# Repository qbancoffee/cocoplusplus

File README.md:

# CoCo++
I spent some time transcribing the CoCo 3 schematic into KiCAD to contribute to the bit preserve project.
Using that schematic, I created a drop in replacement board which I subsequently ordered, assembled, and tested.
At this point I consider that project done and time to move on. If you are interested in the bit preserve
project here is the link.<br>
[Bit Preserve, recreating classic computer schematics](https://github.com/baldengineer/bit-preserve)

So now it's time to have fun....<br>
I want to base this board on the CoCo 3 for several reasons.

- It's the latest real CoCo.
- I never used one in my youth.
- When people upgrade to to the GIME-X, they may want to use their otherwise unused GIME
- If used with a GIME-X then there would be a new CoCo added to the world. 

To start this I stripped the CoCo 3 portion out of the bit-preserve project and
created this repository so that I could make changes to the board that I would like to see. I'm making
this available so that anyone can contribute ideas and expertise.

### Goals
I still don't know what all of the goals are but I'll list some ideas that I've had or that others have mentioned or recommended.
- Having fun
- Mod for potential DMA
- USB keyboard
- Reduce overall size 
- A different form factor
- [Fit it in a polycase ZN-45](https://www.polycase.com/zn-45)
- HDMI or VGA out
- Composite out
- Surface mount components
- 12V power supply with standard barrel connector
- Replace DAC/ADC chip with equivalent circuitry
- Replace SALT chip with equivalent circuitry

### Videos
- [Testing new CoCo 3 board](https://youtu.be/XzGmMZHgejc)
- [Running NitrOS 9 Ease Of Use](https://youtu.be/wSlYcxvCpys)

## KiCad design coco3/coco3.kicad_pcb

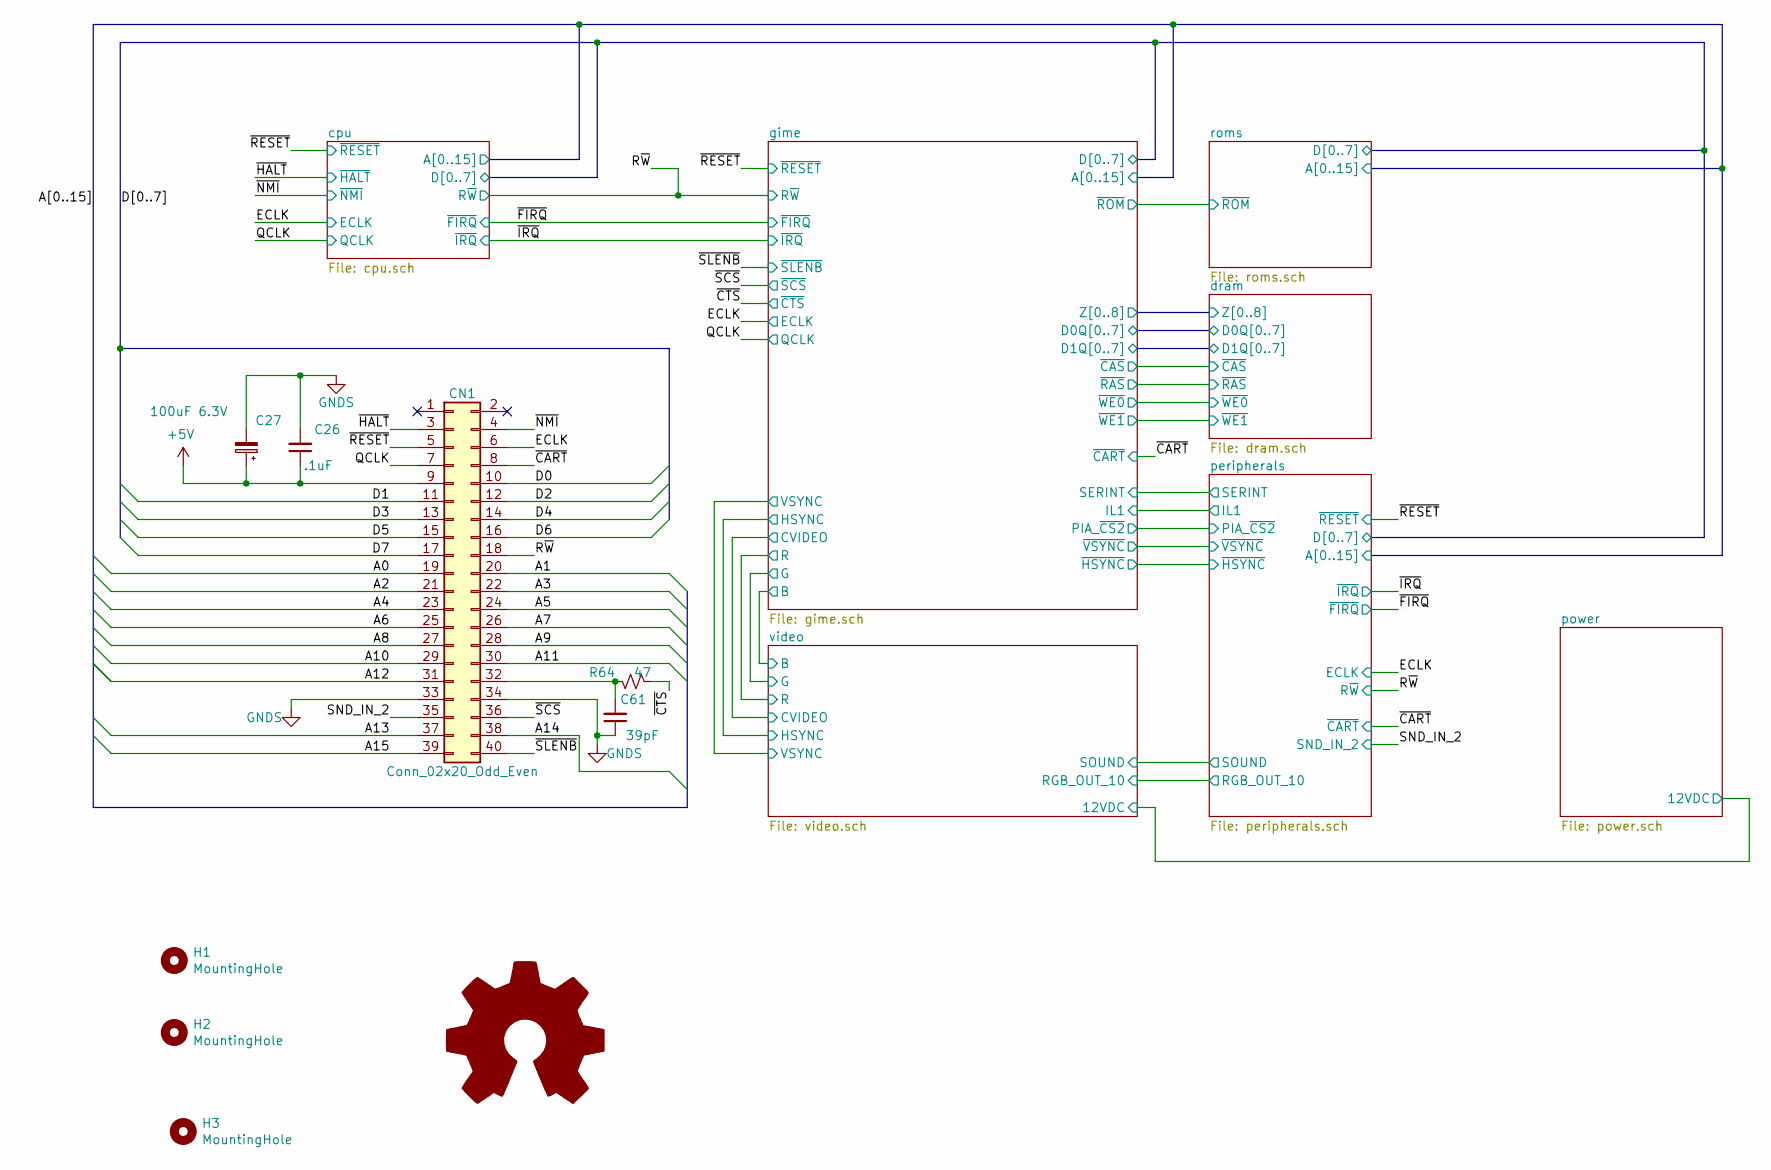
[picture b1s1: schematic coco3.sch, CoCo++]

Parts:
C26: .1uF; C_0805_2012Metric_Pad1.18x1.45mm_HandSolder; Manufacturer part# CL21A106KAYNNNE
C27: 100uF 6.3V; CP_EIA-3528-21_Kemet-B; Manufacturer part# TAJB107K006RNJ
C61: 39pF; C_0805_2012Metric_Pad1.18x1.45mm_HandSolder; Manufacturer part# 0805N390J500CT
CN1: Conn_02x20_Odd_Even; EBC20DRAS; Manufacturer part# EBC20DRAS
H1, H2: MountingHole; MountingHole_3.5mm
H3: MountingHole; coco3_outline_and_layout
R64: 47; R_1206_3216Metric_Pad1.30x1.75mm_HandSolder; Manufacturer part# 1206W4J0470T5E

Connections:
+5V: C26.1, C27.1, CN1.9; also elsewhere on the board
/A0: CN1.19; also elsewhere on the board
/A1: CN1.20; also elsewhere on the board
/A2: CN1.21; also elsewhere on the board
/A3: CN1.22; also elsewhere on the board
/A4: CN1.23; also elsewhere on the board
/A5: CN1.24; also elsewhere on the board
/A6: CN1.25; also elsewhere on the board
/A7: CN1.26; also elsewhere on the board
/A8: CN1.27; also elsewhere on the board
/A9: CN1.28; also elsewhere on the board
/A10: CN1.29; also elsewhere on the board
/A11: CN1.30; also elsewhere on the board
/A12: CN1.31; also elsewhere on the board
/A13: CN1.37; also elsewhere on the board
/A14: CN1.38; also elsewhere on the board
/A15: CN1.39; also elsewhere on the board
/D0: CN1.10; also elsewhere on the board
/D1: CN1.11; also elsewhere on the board
/D2: CN1.12; also elsewhere on the board
/D3: CN1.13; also elsewhere on the board
/D4: CN1.14; also elsewhere on the board
/D5: CN1.15; also elsewhere on the board
/D6: CN1.16; also elsewhere on the board
/D7: CN1.17; also elsewhere on the board
/ECLK: CN1.6; also elsewhere on the board
/QCLK: CN1.7; also elsewhere on the board
/R~W: CN1.18; also elsewhere on the board
/SND_IN_2: CN1.35; also elsewhere on the board
/~CART: CN1.8; also elsewhere on the board
/~CTS: R64.1; also elsewhere on the board
/~HALT: CN1.3; also elsewhere on the board
/~NMI: CN1.4; also elsewhere on the board
/~RESET: CN1.5; also elsewhere on the board
/~SCS: CN1.36; also elsewhere on the board
/~SLENB: CN1.40; also elsewhere on the board
unnamed: C61.2, CN1.32, R64.2

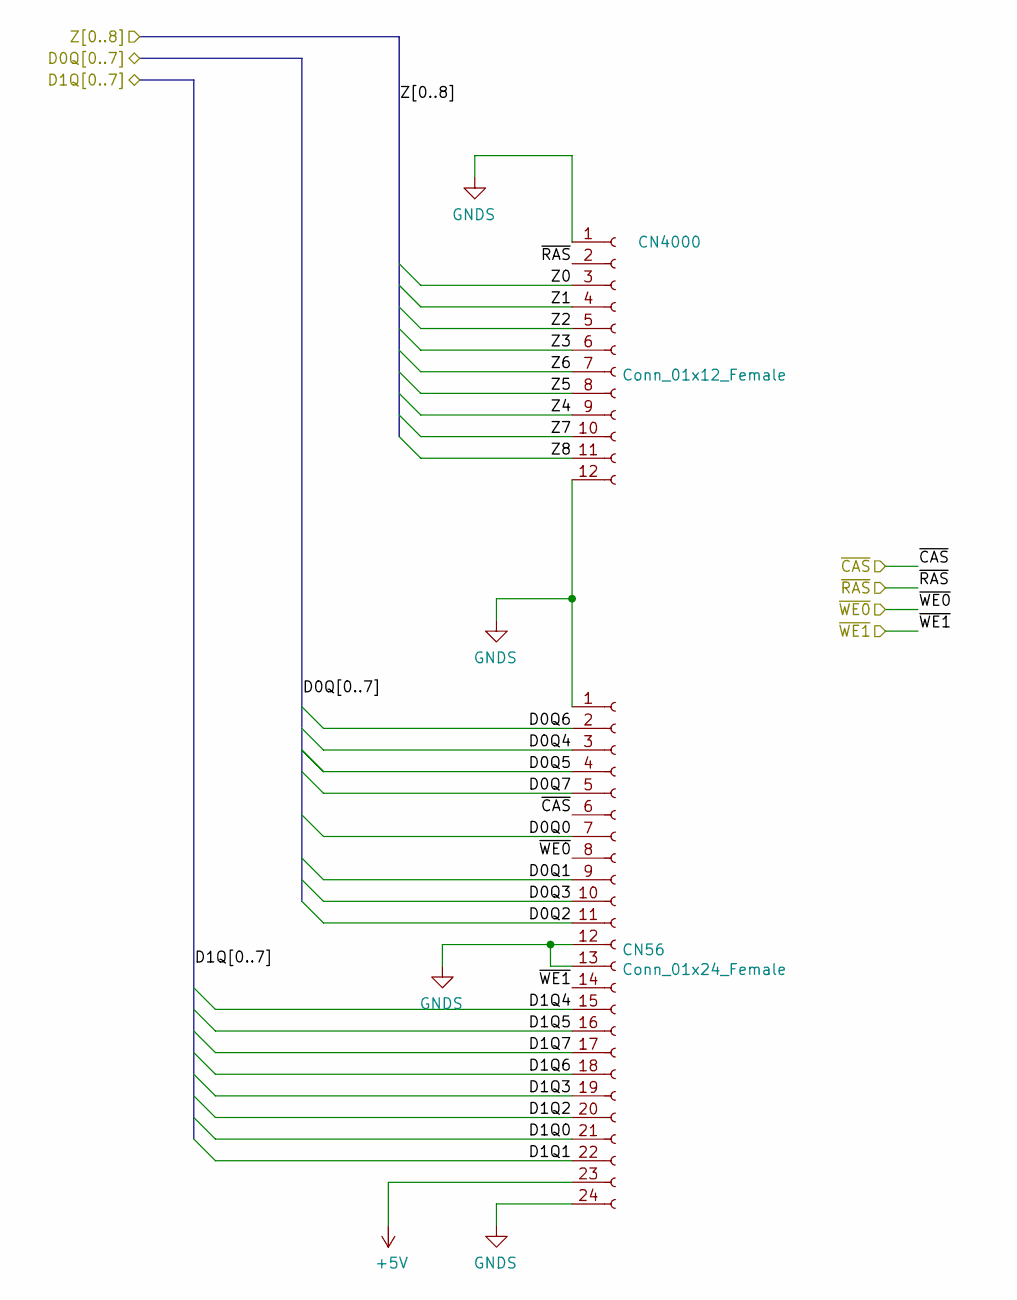
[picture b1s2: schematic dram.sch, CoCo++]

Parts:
CN56: Conn_01x24_Female; PinSocket_1x24_P2.54mm_Vertical; Manufacturer part# PPTC241LFBN-RC
CN4000: Conn_01x12_Female; PinSocket_1x12_P2.54mm_Vertical; Manufacturer part# PPTC121LFBN-RC

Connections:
+5V: CN56.23; also elsewhere on the board
/dram/D0Q0: CN56.7; also elsewhere on the board
/dram/D0Q1: CN56.9; also elsewhere on the board
/dram/D0Q2: CN56.11; also elsewhere on the board
/dram/D0Q3: CN56.10; also elsewhere on the board
/dram/D0Q4: CN56.3; also elsewhere on the board
/dram/D0Q5: CN56.4; also elsewhere on the board
/dram/D0Q6: CN56.2; also elsewhere on the board
/dram/D0Q7: CN56.5; also elsewhere on the board
/dram/D1Q0: CN56.21; also elsewhere on the board
/dram/D1Q1: CN56.22; also elsewhere on the board
/dram/D1Q2: CN56.20; also elsewhere on the board
/dram/D1Q3: CN56.19; also elsewhere on the board
/dram/D1Q4: CN56.15; also elsewhere on the board
/dram/D1Q5: CN56.16; also elsewhere on the board
/dram/D1Q6: CN56.18; also elsewhere on the board
/dram/D1Q7: CN56.17; also elsewhere on the board
/dram/Z0: CN4000.3; also elsewhere on the board
/dram/Z1: CN4000.4; also elsewhere on the board
/dram/Z2: CN4000.5; also elsewhere on the board
/dram/Z3: CN4000.6; also elsewhere on the board
/dram/Z4: CN4000.9; also elsewhere on the board
/dram/Z5: CN4000.8; also elsewhere on the board
/dram/Z6: CN4000.7; also elsewhere on the board
/dram/Z7: CN4000.10; also elsewhere on the board
/dram/Z8: CN4000.11; also elsewhere on the board
/dram/~CAS: CN56.6; also elsewhere on the board
/dram/~RAS: CN4000.2; also elsewhere on the board
/dram/~WE0: CN56.8; also elsewhere on the board
/dram/~WE1: CN56.14; also elsewhere on the board

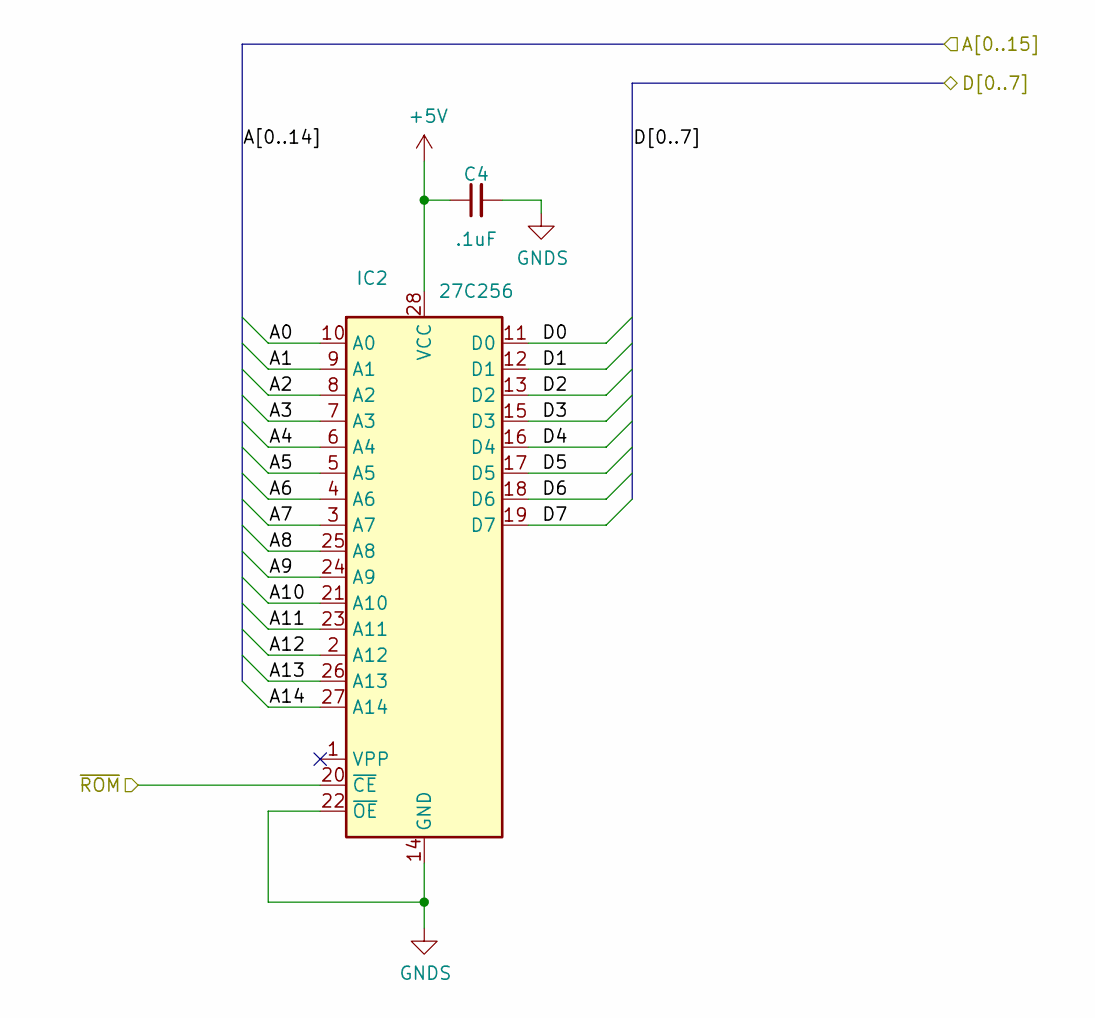
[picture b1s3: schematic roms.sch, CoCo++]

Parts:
C4: .1uF; C_0805_2012Metric_Pad1.18x1.45mm_HandSolder; Manufacturer part# CL21A106KAYNNNE
IC2: 27C256; DIP-28_W15.24mm_Socket; Manufacturer part# AT27C256R-45PU

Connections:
+5V: C4.1, IC2.28 (VCC); also elsewhere on the board
/A0: IC2.10 (A0); also elsewhere on the board
/A1: IC2.9 (A1); also elsewhere on the board
/A2: IC2.8 (A2); also elsewhere on the board
/A3: IC2.7 (A3); also elsewhere on the board
/A4: IC2.6 (A4); also elsewhere on the board
/A5: IC2.5 (A5); also elsewhere on the board
/A6: IC2.4 (A6); also elsewhere on the board
/A7: IC2.3 (A7); also elsewhere on the board
/A8: IC2.25 (A8); also elsewhere on the board
/A9: IC2.24 (A9); also elsewhere on the board
/A10: IC2.21 (A10); also elsewhere on the board
/A11: IC2.23 (A11); also elsewhere on the board
/A12: IC2.2 (A12); also elsewhere on the board
/A13: IC2.26 (A13); also elsewhere on the board
/A14: IC2.27 (A14); also elsewhere on the board
/D0: IC2.11 (D0); also elsewhere on the board
/D1: IC2.12 (D1); also elsewhere on the board
/D2: IC2.13 (D2); also elsewhere on the board
/D3: IC2.15 (D3); also elsewhere on the board
/D4: IC2.16 (D4); also elsewhere on the board
/D5: IC2.17 (D5); also elsewhere on the board
/D6: IC2.18 (D6); also elsewhere on the board
/D7: IC2.19 (D7); also elsewhere on the board
/gime/~ROM: IC2.20 (~CE); also elsewhere on the board

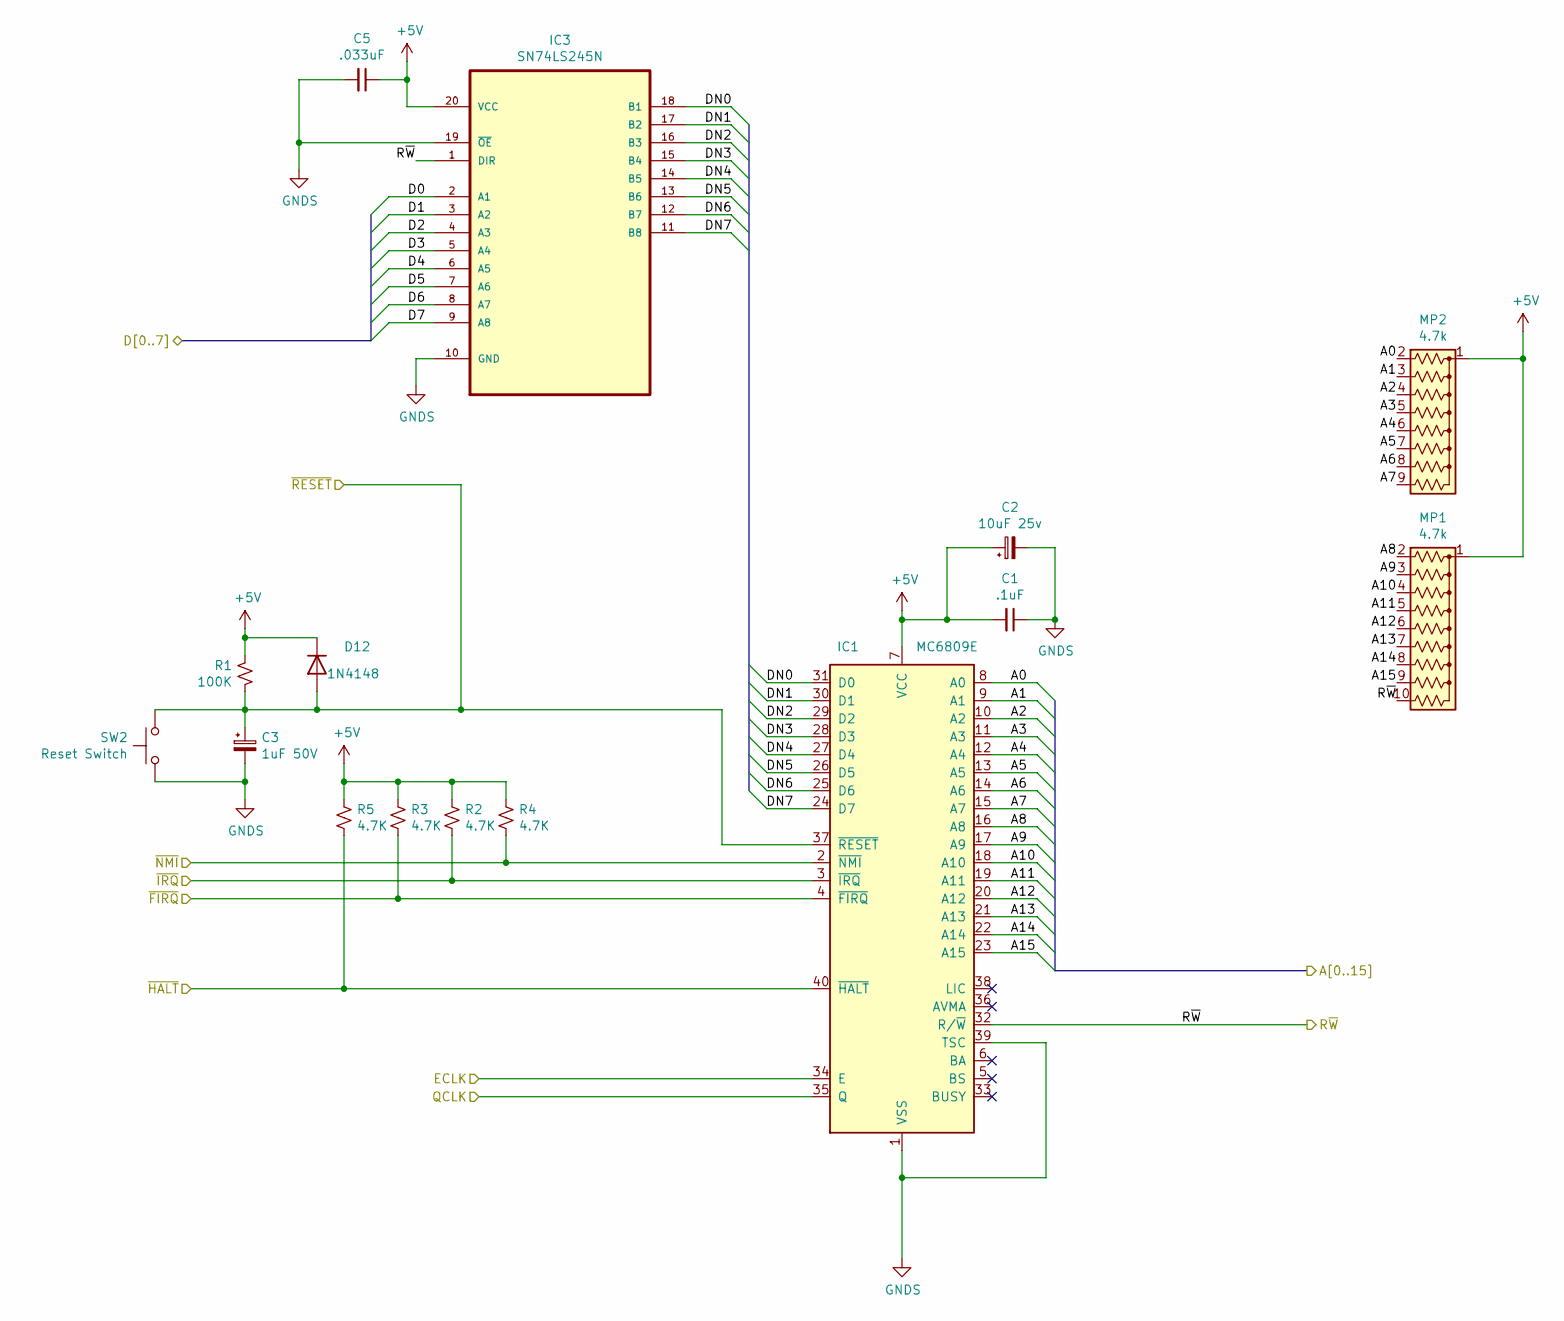
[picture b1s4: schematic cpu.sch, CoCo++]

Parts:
C1: .1uF; C_0805_2012Metric_Pad1.18x1.45mm_HandSolder; Manufacturer part# CL21A106KAYNNNE
C2: 10uF 25v; CP_Elec_4x5.3; Manufacturer part# VE-100M1ETR-0405
C3: 1uF 50V; CP_Elec_4x5.4; Manufacturer part# RVT1H1R0M0405
C5: .033uF; C_0805_2012Metric_Pad1.18x1.45mm_HandSolder; Manufacturer part# 0805B333K500NT
D12: 1N4148; D_SOD-323F; Manufacturer part# 1N4148WS
IC1: MC6809E; DIP-40_W15.24mm_Socket; Manufacturer part# Z-ICS0S40P-W000
IC3: SN74LS245N; SOIC-20W_7.5x12.8mm_P1.27mm; Manufacturer part# SN74LS245DWR
MP1: 4.7k; R_Array_SIP10; Manufacturer part# 770101472P
MP2: 4.7k; R_Array_SIP9; Manufacturer part# 4609H-101-472LF
R1: 100K; R_1206_3216Metric_Pad1.30x1.75mm_HandSolder; Manufacturer part# 1206W4F1003T5E
R2, R3, R4, R5: 4.7K; R_1206_3216Metric_Pad1.30x1.75mm_HandSolder; Manufacturer part# 1206W4F4701T5E
SW2: Reset Switch; B3F3152; Manufacturer part# B3F-3152

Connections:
+5V: C1.2, C2.1, C5.1, D12.1 (K), IC1.7 (VCC), IC3.20 (VCC), MP1.1 (common), MP2.1 (common), R1.1, R2.1, R3.1, R4.1, R5.1; also elsewhere on the board
/A0: IC1.8 (A0), MP2.2 (R1); also elsewhere on the board
/A1: IC1.9 (A1), MP2.3 (R2); also elsewhere on the board
/A2: IC1.10 (A2), MP2.4 (R3); also elsewhere on the board
/A3: IC1.11 (A3), MP2.5 (R4); also elsewhere on the board
/A4: IC1.12 (A4), MP2.6 (R5); also elsewhere on the board
/A5: IC1.13 (A5), MP2.7 (R6); also elsewhere on the board
/A6: IC1.14 (A6), MP2.8 (R7); also elsewhere on the board
/A7: IC1.15 (A7), MP2.9 (R8); also elsewhere on the board
/A8: IC1.16 (A8), MP1.2 (R1); also elsewhere on the board
/A9: IC1.17 (A9), MP1.3 (R2); also elsewhere on the board
/A10: IC1.18 (A10), MP1.4 (R3); also elsewhere on the board
/A11: IC1.19 (A11), MP1.5 (R4); also elsewhere on the board
/A12: IC1.20 (A12), MP1.6 (R5); also elsewhere on the board
/A13: IC1.21 (A13), MP1.7 (R6); also elsewhere on the board
/A14: IC1.22 (A14), MP1.8 (R7); also elsewhere on the board
/A15: IC1.23 (A15), MP1.9 (R8); also elsewhere on the board
/D0: IC3.2 (A1); also elsewhere on the board
/D1: IC3.3 (A2); also elsewhere on the board
/D2: IC3.4 (A3); also elsewhere on the board
/D3: IC3.5 (A4); also elsewhere on the board
/D4: IC3.6 (A5); also elsewhere on the board
/D5: IC3.7 (A6); also elsewhere on the board
/D6: IC3.8 (A7); also elsewhere on the board
/D7: IC3.9 (A8); also elsewhere on the board
/ECLK: IC1.34 (E); also elsewhere on the board
/QCLK: IC1.35 (Q); also elsewhere on the board
/R~W: IC1.32 (R/~W), IC3.1 (DIR), MP1.10 (R9); also elsewhere on the board
/cpu/DN0: IC1.31 (D0), IC3.18 (B1)
/cpu/DN1: IC1.30 (D1), IC3.17 (B2)
/cpu/DN2: IC1.29 (D2), IC3.16 (B3)
/cpu/DN3: IC1.28 (D3), IC3.15 (B4)
/cpu/DN4: IC1.27 (D4), IC3.14 (B5)
/cpu/DN5: IC1.26 (D5), IC3.13 (B6)
/cpu/DN6: IC1.25 (D6), IC3.12 (B7)
/cpu/DN7: IC1.24 (D7), IC3.11 (B8)
/~FIRQ: IC1.4 (~FIRQ), R3.2; also elsewhere on the board
/~HALT: IC1.40 (~HALT), R5.2; also elsewhere on the board
/~IRQ: IC1.3 (~IRQ), R2.2; also elsewhere on the board
/~NMI: IC1.2 (~NMI), R4.2; also elsewhere on the board
/~RESET: C3.1, D12.2 (A), IC1.37 (~RESET), R1.2, SW2.1; also elsewhere on the board

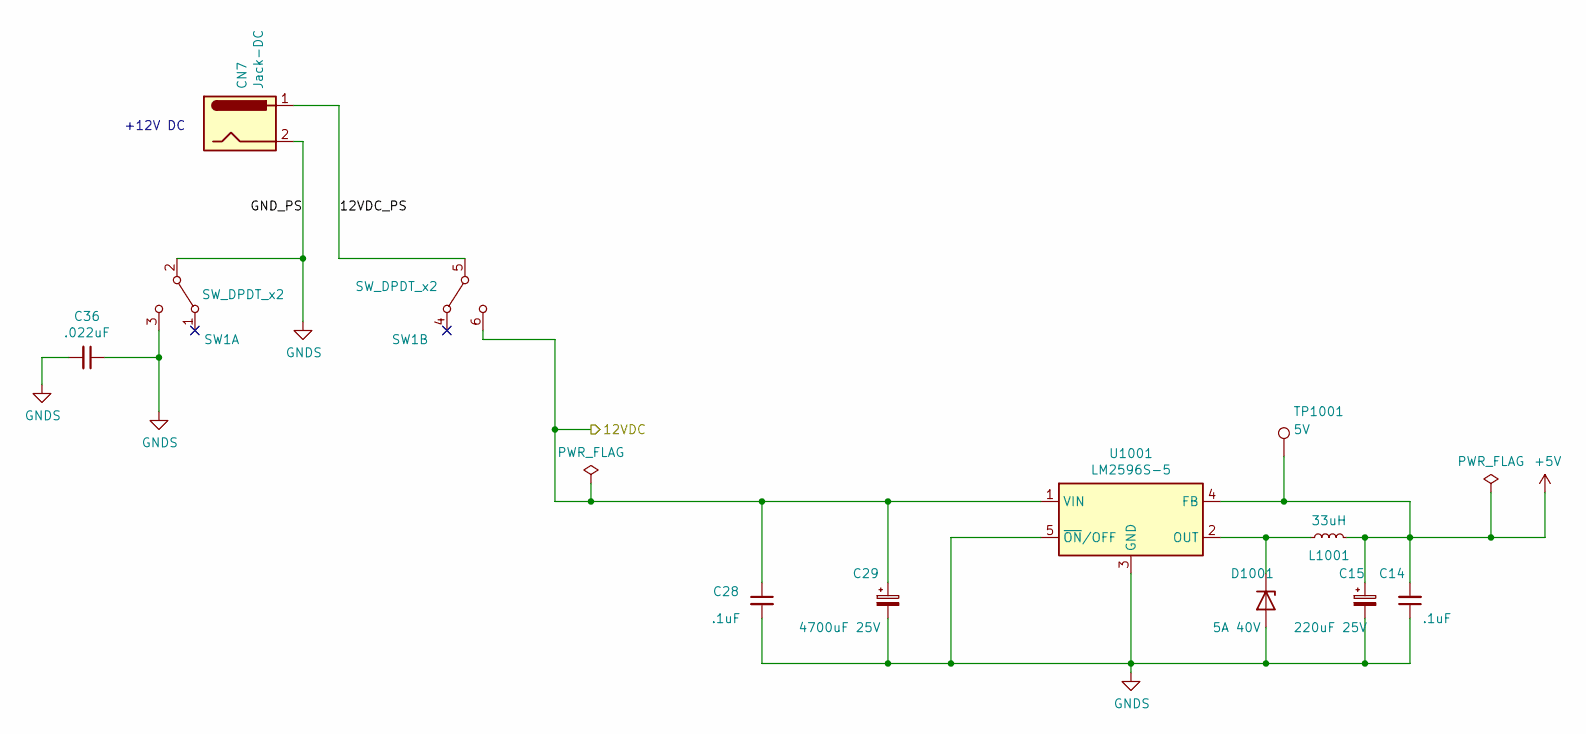
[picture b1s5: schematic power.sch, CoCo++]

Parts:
C14, C28: .1uF; C_0805_2012Metric_Pad1.18x1.45mm_HandSolder; Manufacturer part# CL21A106KAYNNNE
C15: 220uF 25V; CP_Elec_8x10; Manufacturer part# VEJ221M1ETR-0810
C29: 4700uF 25V; CP_Elec_18x22; Manufacturer part# VEJ472M1ETR-1821
C36: .022uF; C_0805_2012Metric_Pad1.18x1.45mm_HandSolder; Manufacturer part# CL21B223KBANNNC
CN7: Jack-DC; BarrelJack_CUI_PJ-063AH_Horizontal; Manufacturer part# PJ-063AH
D1001: 5A 40V; D_SMB; Manufacturer part# SS54B
L1001: 33uH; L_Sumida_CDMC6D28_7.25x6.5mm; Manufacturer part# MWSA0605S-330MT
SW1: SW_DPDT_x2; F2UEE; Manufacturer part# F2UEE
TP1001: 5V; TestPoint_Pad_3.0x3.0mm
U1001: LM2596S-5; TO-263-5_TabPin3; Manufacturer part# LM2596SX-5.0/NOPB

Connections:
+5V: C14.2, C15.1, L1001.2, TP1001.1, U1001.4 (FB); also elsewhere on the board
/power/12VDC: C28.1, C29.1, SW1.6 (C), U1001.1 (VIN); also elsewhere on the board
/power/12VDC_PS: CN7.1, SW1.5 (B)
unnamed: D1001.1 (K), L1001.1, U1001.2 (OUT)

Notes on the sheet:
+12V DC

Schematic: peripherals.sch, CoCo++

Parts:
BREAKOUT0: Conn_01x18_Male; PinHeader_1x18_P2.54mm_Vertical
C6, C7, C13, C47, C48, C1001: .1uF; C_0805_2012Metric_Pad1.18x1.45mm_HandSolder; Manufacturer part# CL21A106KAYNNNE
C16, C17, C20, C21, C25, C49: .022uF; C_0805_2012Metric_Pad1.18x1.45mm_HandSolder; Manufacturer part# CL21B223KBANNNC
C18, C19, C22, C23: 1800pF; C_0805_2012Metric_Pad1.18x1.45mm_HandSolder; Manufacturer part# 0805B182K500NT
C24: 10uF NP; C_Radial_D6.3mm_H5.0mm_P2.50mm; Manufacturer part# UVP1E100MDD1TD
C1002, C1003, C1004: .47uF; C_0805_2012Metric_Pad1.18x1.45mm_HandSolder; Manufacturer part# CL21B474KBFNNNE
CN2: Conn_01x16_Female; PinHeader_1x16_P2.54mm_Vertical; Manufacturer part# 6-520415-6
D5, D1002: 1N4148; D_SOD-323F; Manufacturer part# 1N4148WS
D8, D9, D10, D11: 1KF20-04; D_A-405_P10.16mm_Horizontal; Manufacturer part# D-GE-GEN PURP 75V
FB6, FB8, FB9, FB10: FB_28L0138-10R-10; Manufacturer part# 28L0138-10R-10
IC4, IC5: W65C21N6TPLG-14; PLCC-44_THT-Socket
IC7: SC77526; DIP-20_W7.62mm_Socket; Manufacturer part# 243-20-1-03
IC14: 74LS30; SOIC-14_3.9x8.7mm_P1.27mm; Manufacturer part# SN74LS30DR
IC15: 74LS04; SOIC-14_3.9x8.7mm_P1.27mm; Manufacturer part# SN74LS04DR
J1002: Conn_01x04_Male; PinHeader_1x04_P2.54mm_Vertical
JK1: Left Joystick; CUI_SDS-60J; Manufacturer part# SDS-60J
JK2: Right Joystick; CUI_SDS-60J; Manufacturer part# SDS-60J
JK3: RS232; CUI_SDS-40J; Manufacturer part# SDS-40J
JK4: Cassette; CUI_SDS-50J; Manufacturer part# SDS-50J
Q1001: MMBT9014C; SOT-23; LCSC LCSC
R6, R7, R21, R24, R59: 4.7K; R_1206_3216Metric_Pad1.30x1.75mm_HandSolder; Manufacturer part# 1206W4F4701T5E
R12, R1001, R1008: 10k; R_1206_3216Metric_Pad1.30x1.75mm_HandSolder; Manufacturer part# 1206W4F1002T5E
R13: 100 1W; R_2512_6332Metric_Pad1.40x3.35mm_HandSolder; Manufacturer part# 25121WF1000T4E
R14: 220 1W; R_2512_6332Metric_Pad1.40x3.35mm_HandSolder; Manufacturer part# 25121WJ0221T4E
R66: 7.5K; R_1206_3216Metric_Pad1.30x1.75mm_HandSolder; Manufacturer part# 1206W4F7501T5E
R1002, R1003: 100K; R_1206_3216Metric_Pad1.30x1.75mm_HandSolder; Manufacturer part# 1206W4F1003T5E
R1004, R1005, R1006: 5.1K; R_0805_2012Metric_Pad1.20x1.40mm_HandSolder; Manufacturer part# 0805W8F5101T5E
R1007: 20M; R_1206_3216Metric_Pad1.30x1.75mm_HandSolder; Manufacturer part# 1206W4J0206T5E
RY1: J0971CS5VDC.45; RELAY_J0971CS5VDC.45; Manufacturer part# J0971CS5VDC.45
U1002: MAX3232; SOIC-16_3.9x9.9mm_P1.27mm; Manufacturer part# MAX3232ESE+T
U1003: LM393; TSSOP-8_4.4x3mm_P0.65mm; Manufacturer part# LM393PT

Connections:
+5V: BREAKOUT0.18, C6.2, C7.2, C13.2, C47.2, C48.2, C1003.2, D5.1 (K), IC4.21 (VDD), IC5.21 (VDD), IC14.1, IC14.14 (VCC), R6.1, R7.1, R13.1, R21.2, R24.2, R59.1, R66.2, R1002.1, R1003.1, R1004.2, RY1.A1, U1002.16 (VCC), U1003.8 (V+); also elsewhere on the board
/A0: IC4.39 (RS0), IC5.39 (RS0); also elsewhere on the board
/A1: IC4.38 (RS1), IC5.38 (RS1); also elsewhere on the board
/A5: IC4.26 (CS1), IC15.3; also elsewhere on the board
/D0: IC4.36 (D0), IC5.36 (D0); also elsewhere on the board
/D1: IC4.35 (D1), IC5.35 (D1); also elsewhere on the board
/D2: IC4.34 (D2), IC5.34 (D2); also elsewhere on the board
/D3: IC4.33 (D3), IC5.33 (D3); also elsewhere on the board
/D4: IC4.32 (D4), IC5.32 (D4); also elsewhere on the board
/D5: IC4.31 (D5), IC5.31 (D5); also elsewhere on the board
/D6: IC4.30 (D6), IC5.30 (D6); also elsewhere on the board
/D7: IC4.29 (D7), IC5.29 (D7); also elsewhere on the board
/ECLK: IC4.28 (ENABLE), IC5.28 (ENABLE); also elsewhere on the board
/R~W: IC4.23 (R~W), IC5.23 (R~W); also elsewhere on the board
/gime/IL1: IC14.8; also elsewhere on the board
/gime/PIA_~CS2: IC4.25 (~CS2), IC5.25 (~CS2); also elsewhere on the board
/gime/SERINT: IC4.11 (PB0), U1002.9 (R2OUT); also elsewhere on the board
/gime/~HSYNC: IC5.44 (CA1); also elsewhere on the board
/gime/~VSYNC: IC5.19 (CB1); also elsewhere on the board
/peripherals/CASS_DATA_IN: C24.1, C25.2, JK4.4, R14.2, R1005.2
/peripherals/CASS_DATA_IN_TTL: IC4.3 (PA0), R1004.1, R1007.2, U1003.1; also elsewhere on the board
/peripherals/CASS_MTR_OUT: D5.2 (A), Q1001.3 (C), RY1.A2
/peripherals/CASS_M_ON_TTL: IC4.43 (CA2), Q1001.1 (B), R1001.2
/peripherals/CD_IN_RS232: JK3.1, U1002.13 (R1IN)
/peripherals/CD_IN_TTL: IC4.44 (CA1), U1002.12 (R1OUT)
/peripherals/Color Computer DAC/CASSETTE_OUT: FB6.1; also elsewhere on the board
/peripherals/Color Computer DAC/CASSETTE_SND_IN: C24.2; also elsewhere on the board
/peripherals/Color Computer DAC/D0: IC4.5 (PA2); also elsewhere on the board
/peripherals/Color Computer DAC/D1: IC4.6 (PA3); also elsewhere on the board
/peripherals/Color Computer DAC/D2: IC4.7 (PA4); also elsewhere on the board
/peripherals/Color Computer DAC/D3: IC4.8 (PA5); also elsewhere on the board
/peripherals/Color Computer DAC/D4: IC4.9 (PA6); also elsewhere on the board
/peripherals/Color Computer DAC/D5: IC4.10 (PA7); also elsewhere on the board
/peripherals/Color Computer DAC/SND_ENABLE: IC4.20 (CB2); also elsewhere on the board
/peripherals/HI: IC4.24 (CS0), IC5.24 (CS0), R6.2
/peripherals/IC4_PB4: IC4.15 (PB4), J1002.1
/peripherals/IC4_PB5: IC4.16 (PB5), J1002.2
/peripherals/IC4_PB6: IC4.17 (PB6), J1002.3
/peripherals/IC4_PB7: IC4.18 (PB7), J1002.4
/peripherals/JOY0: C16.1, JK2.1; also elsewhere on the board
/peripherals/JOY1: C17.2, JK2.2; also elsewhere on the board
/peripherals/JOY2: C20.1, JK1.1; also elsewhere on the board
/peripherals/JOY3: C21.2, JK1.2; also elsewhere on the board
/peripherals/K15: BREAKOUT0.15, CN2.15, IC4.13 (PB2), IC5.17 (PB6), R59.2
/peripherals/KR1: BREAKOUT0.1, CN2.1, D11.2 (A), IC5.3 (PA0), IC14.3
/peripherals/KR2: BREAKOUT0.2, CN2.2, D9.2 (A), IC5.4 (PA1), IC14.2
/peripherals/KR3: BREAKOUT0.4, CN2.4, D8.2 (A), IC5.5 (PA2), IC14.12
/peripherals/KR4: BREAKOUT0.5, CN2.5, D10.2 (A), IC5.6 (PA3), IC14.4
/peripherals/KR5: BREAKOUT0.6, CN2.6, IC5.7 (PA4), IC14.11
/peripherals/KR6: BREAKOUT0.7, CN2.7, IC5.8 (PA5), IC14.5
/peripherals/KR7: BREAKOUT0.8, CN2.8, IC5.9 (PA6), IC14.6
/peripherals/PA7: IC5.10 (PA7); also elsewhere on the board
/peripherals/RGB_OUT_10: IC4.14 (PB3); also elsewhere on the board
/peripherals/SELA: IC5.43 (CA2), R24.1; also elsewhere on the board
/peripherals/SELB: IC5.20 (CB2), R21.1; also elsewhere on the board
/peripherals/SERIAL_DATA_IN_RS232: JK3.2, R66.1, U1002.8 (R2IN)
/peripherals/SERIAL_OUT_RS232: JK3.4, U1002.7 (T2OUT)
/peripherals/SER_OUT_TTL: IC4.4 (PA1), U1002.10 (T2IN)
/peripherals/SOUND: R12.1; also elsewhere on the board
/~CART: IC4.19 (CB1), R7.2; also elsewhere on the board
/~FIRQ: IC4.41 (~IRQB), IC4.42 (~IRQA); also elsewhere on the board
/~IRQ: IC5.41 (~IRQB), IC5.42 (~IRQA); also elsewhere on the board
/~RESET: IC4.37 (~RESET), IC5.37 (~RESET); also elsewhere on the board
unnamed: BREAKOUT0.9, CN2.9, IC5.11 (PB0)
unnamed: BREAKOUT0.10, CN2.10, IC5.12 (PB1)
unnamed: BREAKOUT0.11, CN2.11, IC5.13 (PB2)
unnamed: BREAKOUT0.12, CN2.12, IC5.14 (PB3)
unnamed: BREAKOUT0.13, CN2.13, IC5.15 (PB4)
unnamed: BREAKOUT0.14, CN2.14, IC5.16 (PB5)
unnamed: BREAKOUT0.16, CN2.16, IC5.18 (PB7)
unnamed: C18.1, D11.1 (K), JK2.4
unnamed: C19.1, D8.1 (K), JK2.6
unnamed: C22.1, D9.1 (K), JK1.4
unnamed: C23.1, D10.1 (K), JK1.6
unnamed: C49.2, JK1.5, JK2.5, R13.2
unnamed: C1001.1, U1002.3 (C1-)
unnamed: C1001.2, U1002.1 (C1+)
unnamed: C1002.1, U1002.5 (C2-)
unnamed: C1002.2, U1002.4 (C2+)
unnamed: C1003.1, U1002.2 (VS+)
unnamed: C1004.1, U1002.6 (VS-)
unnamed: D1002.1 (K), R1005.1, R1006.2
unnamed: FB6.2, JK4.5
unnamed: FB8.1, JK3.3
unnamed: FB9.2, JK2.3
unnamed: FB10.2, JK1.3
unnamed: IC4.12 (PB1), R12.2
unnamed: IC5.26 (CS1), IC15.4
unnamed: JK4.1, RY1.14
unnamed: JK4.3, RY1.11
unnamed 216: R1002.2, R1006.1, U1003.3 (+); also elsewhere on the board
unnamed 217: R1003.2, R1007.1, R1008.1, U1003.2 (-); also elsewhere on the board

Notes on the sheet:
RY1 is not the original relay the original is no longer made.
R24 is not in the original schematic and it is listed as not used in the parts list. I added it allows the the W65C21N6TPG-14 to work as well.
There are two connectors here. The keyboard connector and a breakout header.

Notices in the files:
parts and their libraries:
Copyright 2016 Accelerated Designs. All rights reserved.
